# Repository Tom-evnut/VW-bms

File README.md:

# VW-bms
Can based decoding of VW bms data

## Teensy 4 version

This is a port for Teensy4.0, it uses a connection PCB to reroute signals to the Teensy3.2 footprint. The board adapter is in kicad format.
On the Teensy4, you can lower the frequency to 150Mhz and it works.
A second can, CAN2, is available on Teensy4.0 to add functionalities or to resolve CAN speed conflicts.

Uncomment //#define USING_TEENSY4 in config.h and select Teensy4.0 as board to use it.

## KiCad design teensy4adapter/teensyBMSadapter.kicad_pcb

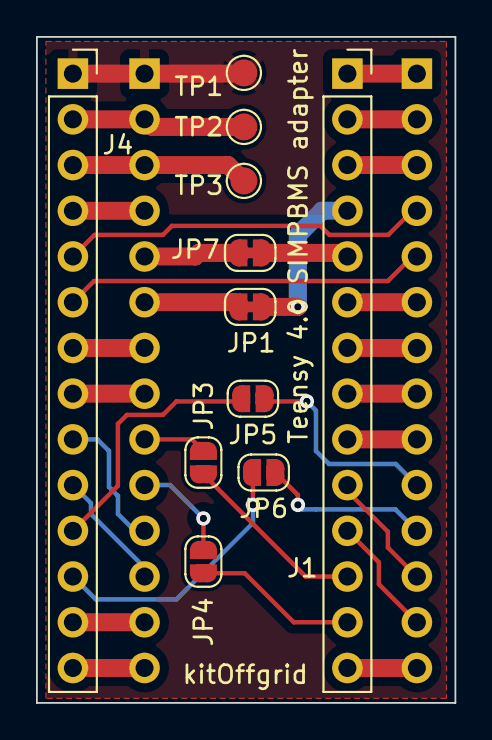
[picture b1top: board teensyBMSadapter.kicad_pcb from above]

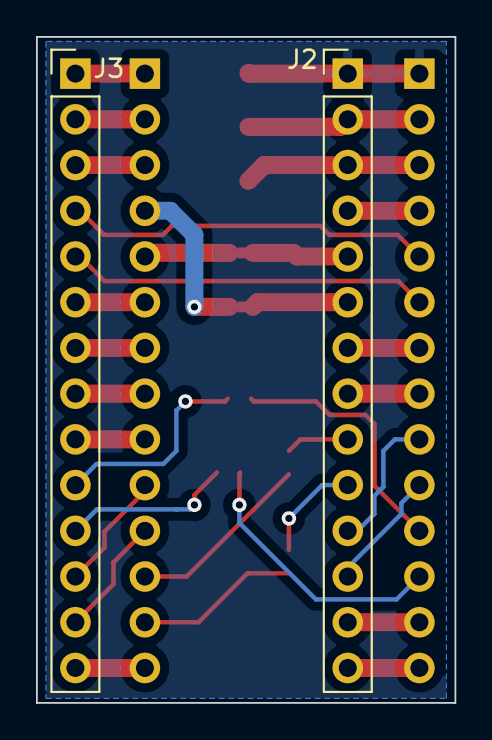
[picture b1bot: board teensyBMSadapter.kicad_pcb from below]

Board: 2 copper layers, 23.2 x 37.0 mm, 13 parts (2 on the bottom side), 34 nets.

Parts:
J1, J4: Conn_01x14_Socket; PinSocket_1x14_P2.54mm_Vertical
J2, J3: Conn_01x14_Pin; PinHeader_1x14_P2.54mm_Vertical
JP1, JP7: SolderJumper_2_Bridged; SolderJumper-2_P1.3mm_Bridged_RoundedPad1.0x1.5mm
JP3, JP4, JP5, JP6: SolderJumper_2_Open; SolderJumper-2_P1.3mm_Open_RoundedPad1.0x1.5mm
TP1, TP2, TP3: TestPoint; TestPoint_Pad_D1.5mm

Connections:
/A2: J1.11, J3.13
/A3: J1.10, J3.12
/A4: J1.9, J3.9
/A5: J1.8, J3.8
/A6: J1.7, J3.7
/A7: J1.6, J3.6
/CANRX1: J1.4, JP1.1 (A)
/CANRX2: J2.2, J4.2, TP2.1
/CANTX1: J1.5, JP7.1 (A)
/CANTX2: J2.3, J4.3, TP3.1
/CS: J4.12, JP6.1 (A)
/GND: J2.1, J4.1, TP1.1
/IO1: J3.4, J4.5
/IO2: J3.5, J4.6
/IO3: J4.11, JP5.1 (A)
/LED/SCK: J1.14, J3.14
/MISO: J2.14, J4.14
/MOSI: J2.13, J4.13
/P17: J3.10, JP5.2 (B)
/P18: J3.11, JP6.2 (B)
/RX3: J2.9, JP3.2 (B)
/RX3T4: J1.12, JP3.1 (A)
/TX3: J2.10, JP4.2 (B)
/TX3T4: J1.13, JP4.1 (A)
unnamed: J1.1, J3.1
unnamed: J1.2, J3.2
unnamed: J1.3, J3.3
unnamed: J2.4, J4.4
unnamed: J2.5, JP7.2 (B)
unnamed: J2.6, JP1.2 (B)
unnamed: J2.7, J4.7
unnamed: J2.8, J4.8
unnamed: J2.11, J4.9
unnamed: J2.12, J4.10

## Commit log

2018-05-12 multi bms board detection
    multi bms board detection
2018-05-13 fixes and tweaks
2018-05-16 updated voltage decoding
2018-06-23 V2 created
    Module IDs need verifying
2018-06-23 clean up decode
2018-06-23 updated CMU mesg IDs
2018-06-23 added can logger
2018-06-23 updated teensycan
2018-06-25 clean up
2018-06-27 fixed voltage conversion
2018-06-28 added storage mode in ESS
2018-06-29 update cmu table
2018-06-29 updated cmu table 2
2018-06-29 clean up debugging cmu ids
2018-06-29 cmu update
2018-06-29 added can filters
2018-06-29 expanded cmu table to 16
2018-06-29 2nd extension cmus
2018-06-29 3 deep cmus
2018-06-29 debug added to cmu detection
2018-06-30 pwm outputs enabled
2018-06-30 pwm output in ess mode
2018-07-02 menu updates
2018-07-03 input pins update
2018-07-09 pwm frequency change
2018-07-09 Watchdog and SOC max fix
2018-07-10 soc fix
2018-07-11 Clearing Modules to dectect comms failure
2018-07-11 alarm added
2018-07-11 alarm
2018-07-11 temp
2018-07-11 update to voltage comms
2018-07-18 Scells added
2018-08-18 moved variable to EEprom
2018-08-18 Invert Current and Voltage SOC added
2018-09-04 Added Contactor Settings
    setup menu 'k'
2018-09-07 Expanded ESSmode
    out 8 is dutycycle based current
    out 7 is SOC based dutycycle
2018-09-07 PWM output updated
2018-09-07 debug off
2018-09-07 update pwm
2018-09-07 pwm update
2018-09-08 PWM TimerFixed
    Created two contactor timers
2018-09-11 updated menu wording
2018-09-16 temp readout
2018-09-16 temp fix
2018-09-16 temp update
2018-09-16 3 temp readout
2018-09-16 3 temp sensor support
2018-10-01 Code Clean Up
2018-10-10 current taper and storage voltage
2018-10-16 Alarm and Warning CAN
2018-10-23 End current and Hex
2018-10-27 HEX added
2018-10-31 Brusa NLG5 Control
2018-10-31 Setable Charger Messages Timing
2018-11-01 updated CAN for Temp
2018-11-01 Updated HEX
2018-11-02 Updated with Ignore and Current Multi
2018-11-03 updated charge control
2018-11-07 updated charger comms
2018-11-07 update charger can
2018-11-07 brusa can changes
2018-11-07 can update
2018-11-07 charger can
2018-11-07 can charger timing
2018-11-07 can change
2018-11-07 can change back
2018-11-07 added 'ncharger'
2018-11-08 Current Analogue Sensor Calibartion added
2018-11-08 5Hz current filter
2018-11-08 Hex Update
2018-11-09 change can debug
2018-11-09 Updated Chargers and Menu
2018-11-11 fix to multi
2018-11-16 ESS Precharge
2018-11-16 Eltek Charger
2018-11-17 menu clean up
2018-11-17 current limit update
2018-11-17 Menu Correction
2018-11-17 Single Input current sensor
2018-11-18 gauge update in all modes
2018-11-21 Eltek Update
2018-11-21 Eltek can update
2018-11-21 Eltek CAN
2018-11-21 Elcon
2018-11-27 extended id
2018-11-27 small change
2018-11-27 can speed adjust
2018-11-27 Revert - Can change not working
2018-11-28 Elcon Charger Working
2018-12-09 No negative Current Request
2018-12-09 Added CSV Output
2018-12-19 Update Debug Screen
2018-12-19 update version
2018-12-19 Updated ESSmode
2019-01-06 ESS mode delays, Current sensor deadband
2019-01-06 Gauge Calibration Update
2019-01-08 always charge on reset and charger endpoint offsets
2019-01-10 Elcon Comms Fix
2019-01-12 VE can storage mode
2019-01-13 Debug digits added
2019-01-19 Out 2 Breaker Trip
2019-01-27 Brusa Charger Settings and Analogue Current Sensor
2019-01-28 Discharge Current Taper
2019-02-03 dash update
2019-02-15 Updated Charger Location
2019-02-16 updated precharge control
2019-03-02 CSV Update
2019-03-02 VW MMD
2019-03-29 can error buffering
2019-03-31 Update missing modules duration
2019-03-31 Updated EEprom Clearing
2019-03-31 updated errors and eeprom
2019-04-01 Series Cells at same times as SOCset
2019-04-01 cell series comparison
2019-04-04 Contactor Feedback update
2019-04-04 ESS Mode Charging Fix
2019-04-04 ESSmode Update
2019-04-06 Added Measurement Difference Error
2019-04-06 update to writing cell values
2019-04-06 updated voltage delta
2019-04-06 clean up warnings can error
2019-04-06 updated start up
2019-04-06 no boot without cells
2019-04-06 updated no cells present
2019-04-06 error now causes shutdown
2019-04-09 Can Timer message hidden
2019-04-09 Updated module reporting Can timeout error
2019-04-23 Screen Serial Bus started
2019-04-29 Coda Charger
2019-04-30 Coda Fix
2019-05-07 Disclaimer and Liscence
2019-05-11 Battery Lock Out
2019-05-12 Revert "Battery Lock Out"
    This reverts commit 6e0612401be90027f5c4ff666078e2b4b802112f.
2019-05-23 Ncur fix
2019-11-22 temperature comparisoion from Avg to Low and High
2019-11-22 firmware release Temp Fix
2019-11-24 SOC reset 100% in ESSmode
2019-12-03 fix shunt trip on start
2019-12-06 cleaned up error reporting
2020-02-11 fixed cab sensor
2020-02-11 .hex release
2020-02-13 Updated SOC Setting
2020-02-14 Correction can info filtering
2020-03-21 Serial Display update
2020-06-11 Update ESSmode
2020-08-18 Removed Voltage can filtering
2020-10-21 added more ids
2021-02-06 13s Cell Voltages
2021-02-06 Added 13s Temp Decode
2021-02-06 Temperature Decoding canbus GTE and newer
    Decoding temperatures for all VW modules
2021-02-06 Debug temp decoding
2021-02-06 VE canbus updated
    update to included expanded victron canbus
2021-02-06 comment out Error resetting ESS mode
2021-02-06 Error Reason update and Clear module enable
2021-02-06 Correct clear module and Error Reason
2021-02-06 modified module clearing
2021-03-11 fix Boot status looping
2021-03-31 Special Cab500 0x3C1
2021-04-08 increase comms check window
    3x increase to 10,000 instead of 3,000
2021-04-24 canbus current sensor variants
2021-04-27 ESSmode Temp recovery
2021-04-28 longer comms check gap, and temp comms check
2021-06-14 IVTs Fix
2022-02-20 added DBC and Can Id info
2022-02-21 Balancing testing in Code
2022-02-21 corrected canbus for balance feedback
2022-02-25 Balancing Implemented
    Balancing is verified and working now.
2022-03-03 Removing more Debug including stopping Can
2022-03-25 Changes to Average Calcs to account ID3
    ID3 single slave modules pretend to have 4 modules, this was messing with average calculations.
    These are now updated to ignore "empty" modules
2022-05-04 Correction in balancing
    Update to Balancing for cells 9-14
2022-05-05 ESSmode Zero Current Charger Output Off
    ESSmode Zero Current Charger Output Off
2022-06-02 SOC now with Low Cell and SOC EEprom Save
    SOC voltage logic now looks at Lowest Cell Voltage
    SOC on Teensy Brown out saved to EEProm
2022-07-06 ISA Current Shunt Canbus Correction
2022-07-14 MEB temperature support Added
    MEB Temperature feedback decode, one temp sensor identified
    Cleaned up debug screen when MEB specific messages found
2022-07-15 Added balancing pause and ignore
2022-07-17 changed MEB temp identification transfer into BMSmodule
2022-07-21 balancing pause canbus
2022-08-18 Balancing clean up
    Remove test code,
    Reduce messages
    Increase modules up to 12.
2022-08-18 Increase rate Balance Command
2022-09-07 Fixed 13s system
    corrected to recieve 13s VW BMS again
2022-09-08 Correct Temp Message Decode VW 13S
2022-10-24 Pylon Can Added
2022-10-26 Isa Scale Clean up
2022-10-26 Surpress Balancing debugging
2022-11-27 Fixed CAN IDs for module 3 balancing commands
2022-11-29 Revert "Merge pull request #2 from vanbergeijk/master"
    This reverts commit 513294c4ae7a32916190fd0826ed09cb7fb538d3, reversing
    changes made to d7fb3f79d0b6b32c0e030d696585d64abcc649bf.
2023-03-11 Adding support for the Mitsubishi Outlander Charger
2023-03-16 Fixing type in case statement
2023-03-30 Correction Switch Case for Outlander Charger
    Added 12A dc current request limit for outlander charger.
2023-05-10 Discharge Check on Key On
    Check if not under discharge voltage before turning on with key on
2023-05-11 SOC Start Up Correction
    Reading from Memory works now
    Start up delay functions corrected when reading from Memory
2023-06-14 Kicad: adding an adpater pcb for Teensy4.0
    This adapter reroutes the CAN1 pins, UART3 and some IOS. The firmware
    must be edited a little to make this work.
2023-06-14 kicad: connected UART3 because of the tesla module.
2023-06-14 Swaped some pins according to the adapter schematic revision
2023-06-14 gitignore: ignore the gerber files
2023-07-15 [DEV] Renamed config.h to lower case, did not pass compilation on linux.
2023-07-18 compilation warnings, removing them and using FlexCAN_T4
2023-07-18 More warning cleaning
2023-07-18 Flexcan fix the define
2023-07-18 Get the headers sorted out for FlexCAN_T4
2023-07-19 Shutdown SOC Save Fix
2023-07-29 [DEV] Adapt to Teensy 4 library
2023-08-02 Watchdog, replace with a library, again from tonton81, thanks
2023-08-02 Low voltage deteector: removing the code for teensy 4
    The Teensy 4 seems to have no low voltage detector.
2023-08-02 Can0.available() n on Flex_CanT4, read() returns 0 instead.
2023-08-09 Compiling firmware, not tested.
2023-09-20 Allowance for 10s Modules
2023-12-27 Just one comment on the library sources, seems to work at 150Mhz when comparing the output to the original Teensy3.2.
2023-12-28 Adding closed solder jumpers to the CAN bus pins
2023-12-28 Fix: the can bus in use is the first one, not the second.
    However we can add more connectors later, like to separate the Victron
    can to the battery pack can. If we redesign for the Teensy4.1, we can
    even have 3 can buses.
2023-12-29 Use an enum for the menu codes to clarify the program.
2023-12-29 Serial console rework such as to buffer configuration command lines.
2023-12-29 FIX: only use the newline buffer once a line is read.
    The user must now press a key + return to send a command.
2023-12-30 output console: adds error message details.
2023-12-30 Voilà, works on teensy4.0
2023-12-30 Clean up before the pull request.
2023-12-30 Comme back to 3.2 to merge with master.
2023-12-30 Fixing merge damage on a VWBMSV2.ino.lst
2023-12-30 Fixing merge damage on VWBMSV2.ino.lst
2024-01-01 Bump up firmware version, and fix a directive
    Just found out that this work was already in martinezz fork. However it
    is not arduino.
2024-03-18 Updated Alarm and warning
2024-03-27 Balancing 13S correction
2024-03-27 Correction 13S 2
